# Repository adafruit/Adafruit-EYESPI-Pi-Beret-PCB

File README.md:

## Adafruit EYESPI Pi Beret PCB

<a href="http://www.adafruit.com/products/5783"><br/>
Click here to purchase one from the Adafruit shop</a>

PCB files for the Adafruit EYESPI Pi Beret. 

Format is EagleCAD schematic and board layout
* https://www.adafruit.com/product/5783

### Description

Raspberry Pi's make for handy lil computers, but they're really wonderful when you can connect all sorts of nifty hardware to them: color TFT or E-Ink displays, and sensors are our go-to favorites. Even better is when we make it fast and effortless to wire these up. With this new EYESPI Pi Beret there's no more counting pins or noodling with a breakout board. This slim HAT plugs in and gives you lots of hardware connection options so that many projects become plug-and-play.

Our most recent display breakouts have come with a new feature: an 18-pin "EYE SPI" standard FPC connector with flip-top connector. This is intended to be a sort-of "STEMMA QT for displays" - a way to quickly connect and extend display wiring that uses a lot of SPI pins. In this case we need a lot of SPI and accessory pins, and we want to be able to use long distances, so we go with an 18-pin 0.5mm pitch FPC.

With such a slim and flexible cable, it's easy to have displays anywhere without them physically attached to the Pi like in our PiTFTs. Accessorize with big bold colorful displays or power-sipping E-Ink. 

Don't forget you'll also want an 18-pin EYESPI FPC cable. And of course one of our EYESPI displays too - look for the EYESPI logo on the back to know you've got one that can clip in.

* MOSI/MISO/SCK SPI pins are connected to the default SPI port on the Raspberry Pi
* SDA/SCL I2C pins are connected to the default I2C port on the Pi
* Display CS on Raspberry Pi CE 0
* Display DC on Raspberry Pi GPIO #25
* Display Reset on Raspberry Pi GPIO #27
* Display Busy on Raspberry Pi GPIO #17 (used for E-Inks)
* Display Backlight on Raspberry Pi GPIO #18 (there's a jumper to cut/disable this if you want to use the PWM output for other uses like NeoPixels)
* Touch CS on Raspberry Pi CE 1
* Touch IRQ on Raspberry Pi GPIO #24

The remaining EYESPI pins are not connected, leaving you with plenty of GPIO for other accessory boards.

We also have a Stemma QT connector for the I2C port, to make connecting all sorts of Qwiic/Stemma QT devices super easy, two tactile switches on GPIO #5 and #6 and a slide switch on GPIO #13 which you can use for any sort of interface project or configuration.

Display and EYESPI cable are not included.

### License

Adafruit invests time and resources providing this open source design, please support Adafruit and open-source hardware by purchasing products from [Adafruit](https://www.adafruit.com)!

Designed by Limor Fried/Ladyada for Adafruit Industries.

Creative Commons Attribution/Share-Alike, all text above must be included in any redistribution. 
See license.txt for additional details.

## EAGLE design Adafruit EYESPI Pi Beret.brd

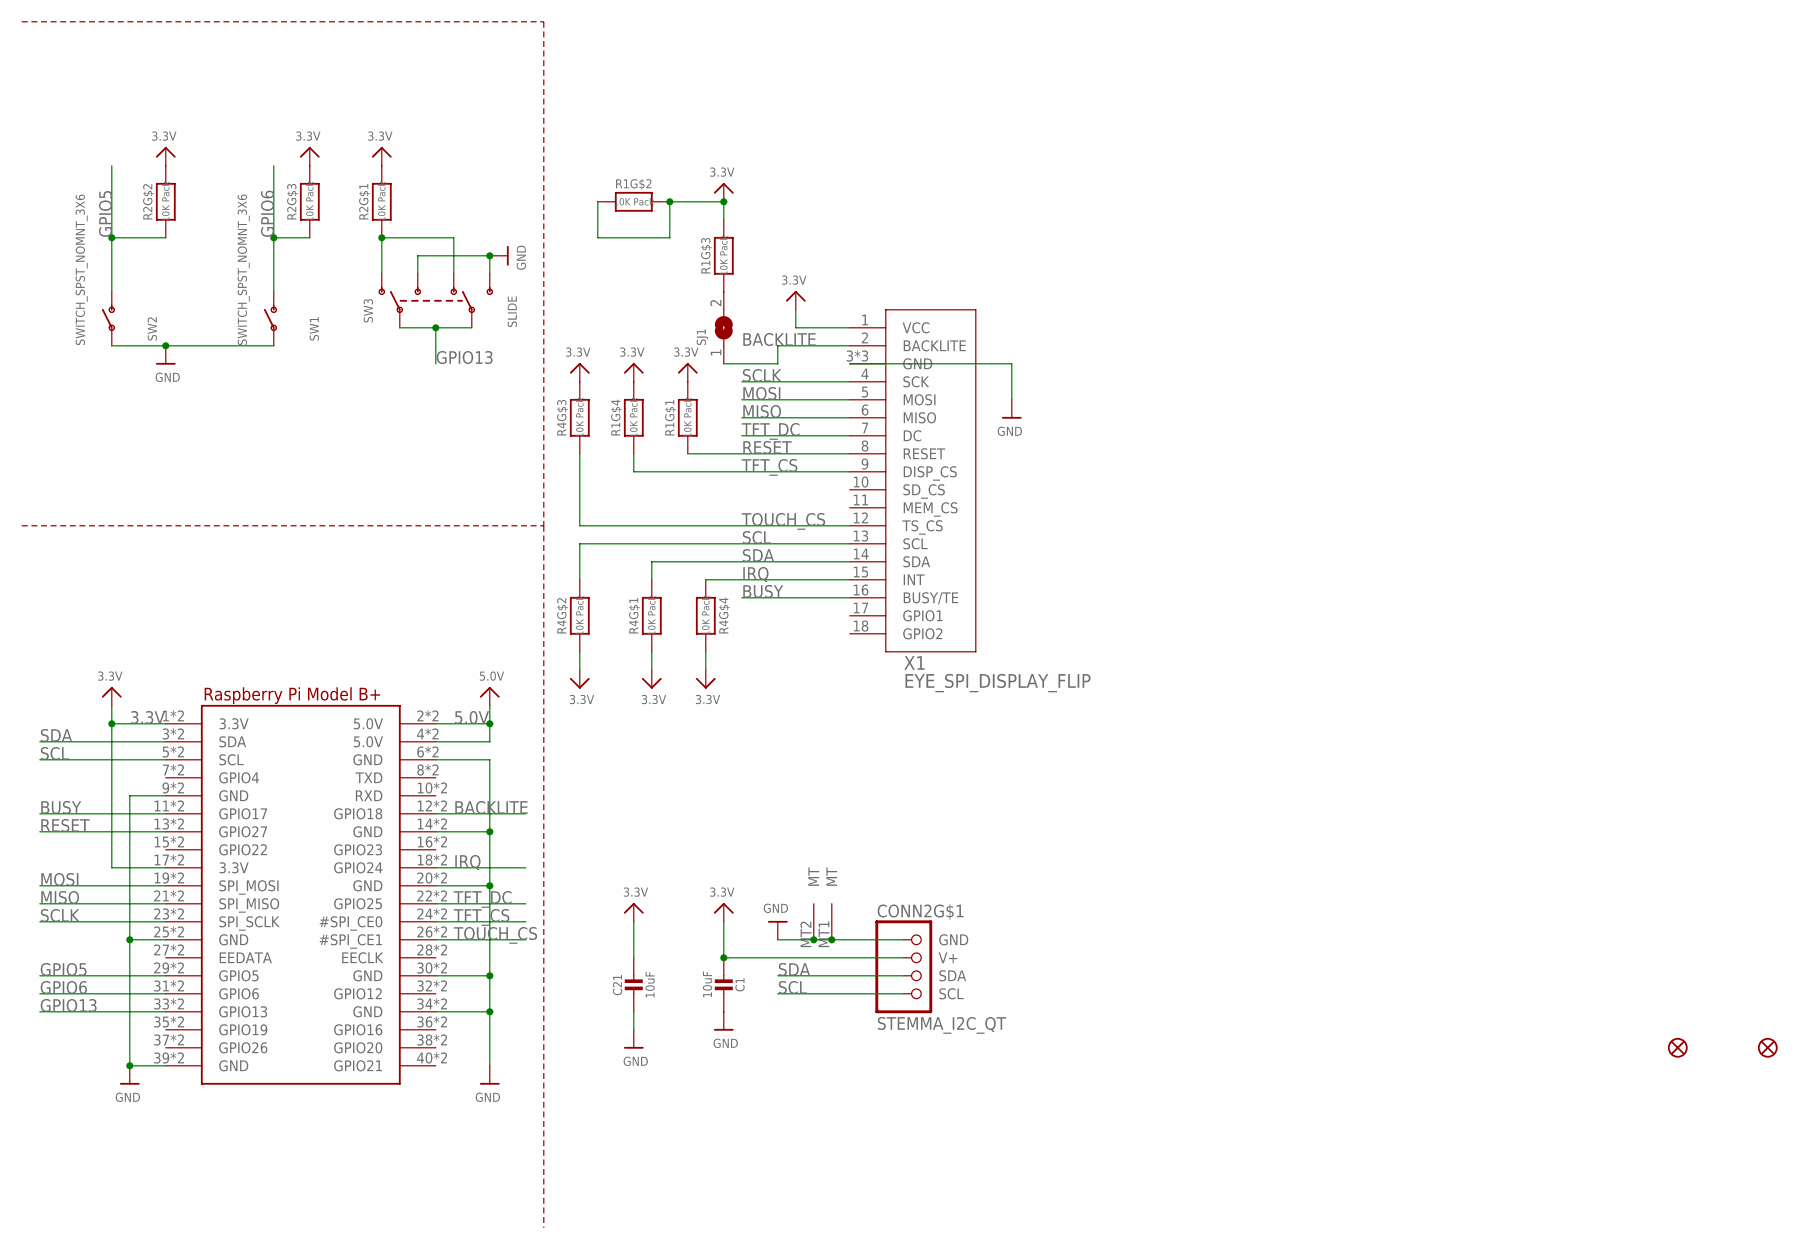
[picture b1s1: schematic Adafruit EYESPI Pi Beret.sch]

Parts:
C1, C21: 10uF; 0805-NO
CONN2: STEMMA_I2C_QT; JST_SH4
FID1, FID4: FIDUCIAL_1MM
R1, R2, R4: 10K Pack; RESPACK_4X0603
RPI2: RASPBERRYPI_BPLUS_2X20_THMSMT; RASPI_2X20_THMSMT
SJ1: SOLDERJUMPERCLOSED; SOLDERJUMPER_CLOSEDWIRE
SW1, SW2: SWITCH_SPST_NOMNT_3X6; TACTILE_3X6MM
SW3: SLIDE; EG1390
X1: EYE_SPI_DISPLAY_FLIP; EYE_SPI_DISPLAY_BOTCONTACT

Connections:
3.3V: C1.2, C21.1, CONN2.2 (V+), R1.2 (1), R1.5 (2), R1.6 (2), R1.7 (2), R1.8 (2), R2.6 (2), R2.7 (2), R2.8 (2), R4.1, R4.2 (1), R4.5 (2), R4.6 (2), RPI2.1 (3.3V), RPI2.17 (3.3V), RPI2.S1 (3.3V), RPI2.S17 (3.3V), X1.1 (VCC)
5.0V: RPI2.2 (5.0V), RPI2.4 (5.0V), RPI2.S2 (5.0V), RPI2.S4 (5.0V)
BACKLITE: RPI2.12 (GPIO18), RPI2.S12 (GPIO18), SJ1.1, X1.2 (BACKLITE)
BUSY: RPI2.11 (GPIO17), RPI2.S11 (GPIO17), X1.16 (BUSY/TE)
GND: C1.1, C21.2, CONN2.1 (GND), CONN2.MT1 (MT), CONN2.MT2 (MT), RPI2.6 (GND), RPI2.9 (GND), RPI2.14 (GND), RPI2.20 (GND), RPI2.25 (GND), RPI2.30 (GND), RPI2.34 (GND), RPI2.39 (GND), RPI2.S6 (GND), RPI2.S9 (GND), RPI2.S14 (GND), RPI2.S20 (GND), RPI2.S25 (GND), RPI2.S30 (GND), RPI2.S34 (GND), RPI2.S39 (GND), SW1.P$1, SW2.P$1, SW3.S1, SW3.S2, X1.3 (GND), X1.SUPPORT1 (GND), X1.SUPPORT2 (GND)
GPIO5: R2.2 (1), RPI2.29 (GPIO5), RPI2.S29 (GPIO5), SW2.P$2 (S)
GPIO6: R2.3 (1), RPI2.31 (GPIO6), RPI2.S31 (GPIO6), SW1.P$2 (S)
GPIO13: RPI2.33 (GPIO13), RPI2.S33 (GPIO13), SW3.P1, SW3.P2
IRQ: R4.4 (1), RPI2.18 (GPIO24), RPI2.S18 (GPIO24), X1.15 (INT)
MISO: RPI2.21 (SPI_MISO), RPI2.S21 (SPI_MISO), X1.6 (MISO)
MOSI: RPI2.19 (SPI_MOSI), RPI2.S19 (SPI_MOSI), X1.5 (MOSI)
unnamed: R1.3 (1), SJ1.2
unnamed: R2.1, SW3.O1, SW3.O2
RESET: R1.1, RPI2.13 (GPIO27), RPI2.S13 (GPIO27), X1.8 (RESET)
SCL: CONN2.4 (SCL), R4.7 (2), RPI2.5 (SCL), RPI2.S5 (SCL), X1.13 (SCL)
SCLK: RPI2.23 (SPI_SCLK), RPI2.S23 (SPI_SCLK), X1.4 (SCK)
SDA: CONN2.3 (SDA), R4.8 (2), RPI2.3 (SDA), RPI2.S3 (SDA), X1.14 (SDA)
TFT_CS: R1.4 (1), RPI2.24 (#SPI_CE0), RPI2.S24 (#SPI_CE0), X1.9 (DISP_CS)
TFT_DC: RPI2.22 (GPIO25), RPI2.S22 (GPIO25), X1.7 (DC)
TOUCH_CS: R4.3 (1), RPI2.26 (#SPI_CE1), RPI2.S26 (#SPI_CE1), X1.12 (TS_CS)

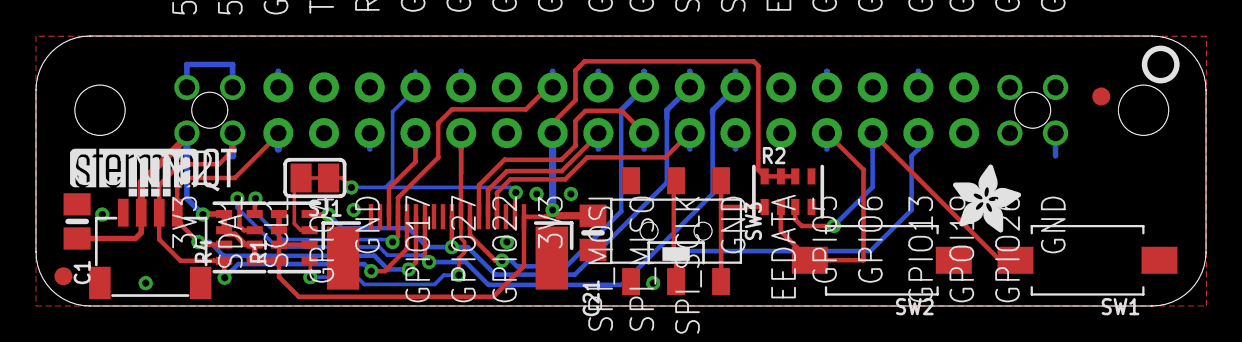
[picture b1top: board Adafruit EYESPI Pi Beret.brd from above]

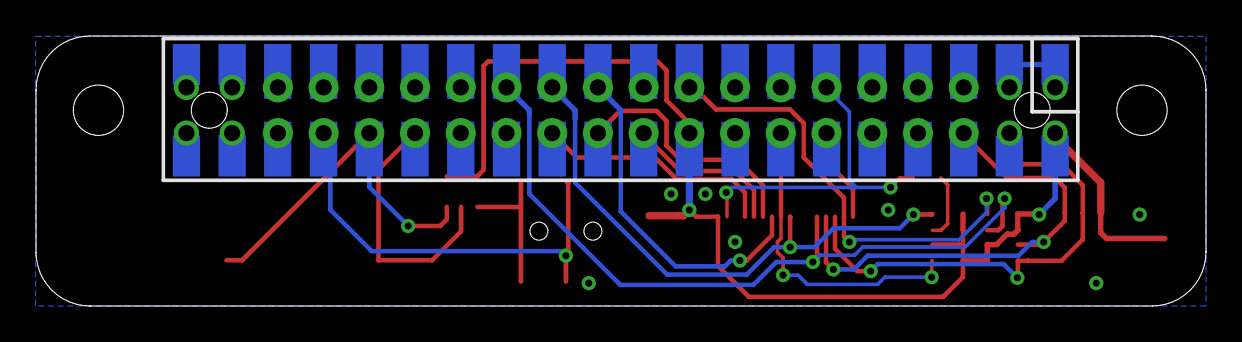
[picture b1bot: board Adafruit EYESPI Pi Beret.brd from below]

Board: 2 copper layers, 65.0 x 15.0 mm, 24 parts (2 on the bottom side), 20 nets.

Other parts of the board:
PLABEL0: PLABEL0
PLABEL1: PLABEL1
PLABEL2: PLABEL2
PLABEL3: PLABEL3
PLABEL4: PLABEL4
PLABEL5: PLABEL5
PLABEL6: PLABEL6
U$9: PCBFEAT-REV-040
U$24: ADAFRUIT_3.5MM
U$30: STEMMAQT

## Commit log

2023-08-30 Add board files.

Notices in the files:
parts and their libraries:
microbuilder: This work is placed in the public domain, and may be freely used for commercial and non-commercial work with the following conditions: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
